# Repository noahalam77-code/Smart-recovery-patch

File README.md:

# TheraPatch

## Repository file structure
- BOM: JCLPCB BOM & regular BOM
- CADfiles: STEP files, STL files, and assembly notes
- PCB: PCB files, Gerber files, schematic images, and PCB images
- Firmware: Code & flashing instructions

## What it is
TheraPatch is a handheld therapeutic device designed to help mitigate the effects of injuries such as bruises, sprains, minor cuts, and more. By using a reverse-polarity system via an H-bridge, TheraPatch can heat the affected area (dilating blood vessels) or cool it (constricting blood vessels), both of which have been shown to help with injury healing at certain temperatures (which TheraPatch can achieve). 

## Motivation
I created TheraPatch with the primary motivation of helping people with common sports/activty related injuries while maintaining an efficient device to do so. Most of the time, when you have a bruise or scrape, you'd rely on disposable ice packs or inefficient heating pads, which are wasteful and time-consuming for long-term use. TheraPatch offers an effective, infinitely reusable solution to this. Instead of freezing water for 3-4 hours or boiling a heatpack everytime you need to reuse it, all you do with TheraPatch is plug and play. It's effective for athletes and normal people.

## Use of TheraPatch
To use the TheraPatch, first ensure your battery/wall adapter is plugged in. Then locate the 4 buttons on the top of the device; these buttons will allow you to set your desired parameters by moving through the menus: mode (hot/cold), set temp, and set time. After your desired settings are set, click the start button to initiate your therapy session, and place the side with the Peltier facing out against the affected area

## How it works
The TheraPatch looks like a simple black-and-white hot-cold block, but its guts are far more advanced. In electronics, generating heat is relatively simple. Electrons bump into each other rapidly in the wire, vibrating and thus creating the heat we feel. This is the easy part; cooling is the real engineering challenge. To cool it, I used a Peltier module, which transfers heat from one side to the other. Now, this needs to be driven by a heatsink and a fan to effectively cool. To achieve heating and cooling on the same side, I used an H bridge. The H-bridge module reverses the polarity in a Peltier module, meaning that when one side is positive and the other is negative, it cools; vice versa. All of this is controlled by a custom 4-layer PCB I designed in KiCad, with an ATmega328P as my microcontroller. The firmware reads a thermistor pressed against the Peltier plate and uses a bang-bang controller to turn the Peltier on/off to reach the desired temperature. This is all run by a rechargeable 12V battery, which charges via USB-C or a 12V wall adapter. These components are combined in a logical order in a CAD-designed box with a hole for all the input plugs and vent fans for air circulation.

Here are images of my project

## CAD imgaes:

## Link to Onshape case:

https://cad.onshape.com/documents/d627d659f05dae60588ec801/w/ad74ef98cd2d7a13cb59f9ec/e/f50ed022a94792dc2cfe6130?renderMode=0&uiState=6a4947abb17d022f5d41873a

# PCB (Signal Layer and ground):

## F.cu (signal traces and ground):

## In1.cu(ground):

## In2.cu (5V & 12V power)

## B.cu (signal traces and ground):

## 3D:

# Schematic (wiring diagram):

## Pic_1:

## Pwr:

## BOM(main)

| Item | Quantity | Unit price | Total price | Descrption | Link |
|------|----------|-----------|-------------|------------|------|
| Fan | 1 | 4.81 | 4.81 | Facliate heaitng & cooling | [Link](https://www.aliexpress.us/item/3256808462428286.html?spm=a2g0o.productlist.main.1.6babkeHNkeHNko&algo_pvid=c39052da-f6dd-4b67-816a-d90e786c586d&algo_exp_id=c39052da-f6dd-4b67-816a-d90e786c586d-0&pdp_ext_f=%7B%22order%22%3A%2262%22%2C%22eval%22%3A%221%22%2C%22fromPage%22%3A%22search%22%7D&pdp_npi=6%40dis%21USD%2111.50%214.79%21%21%2178.10%2132.53%21%402101d6ff17774285328603962e8757%2112000046088904920%21sea%21US%210%21ABX%211%210%21n_tag%3A-29910%3Bd%3Ad6b644bf%3Bm03_new_user%3A-29895%3BpisId%3A5000000204886261&curPageLogUid=VweLjIS1lGkI&utparam-url=scene%3Asearch%7Cquery_from%3A%7Cx_object_id%3A1005008648743038%7C_p_origin_prod%3A) |
| Peltier | 1 | 3.90$ | $3.90 | Cool and heat | [Link](https://www.aliexpress.us/item/3256806863842277.html?src=google&gatewayAdapt=glo2usa) |
| Heatsink | 2 | 4.80$ | $9.79 | Disspate heat | [Link](https://www.amazon.com/Awxlumv-Aluminum-60mmx60mmx15mm-Conductive-Amplifier/dp/B0DNLXD4NL) |
| LCD screen | 1 | 0.9900$ | 0.9900$ | Displaying modes | [Link](https://www.aliexpress.us/item/3256807264700302.html?spm=a2g0o.productlist.main.15.3bb1HGrhHGrhWv&algo_pvid=f071bd73-714c-4717-acaa-3f74ef8deb17&algo_exp_id=f071bd73-714c-4717-acaa-3f74ef8deb17-14&pdp_ext_f=%7B%22order%22%3A%223710%22%2C%22eval%22%3A%221%22%2C%22fromPage%22%3A%22search%22%7D&pdp_npi=6%40dis%21USD%213.14%210.99%21%21%213.14%210.99%21%4021030a6217776832914577048eb84d%2112000040806152744%21sea%21US%210%21ABX%211%210%21n_tag%3A-29910%3Bd%3Ad6b644bf%3Bm03_new_user%3A-29895%3BpisId%3A5000000203537378&curPageLogUid=GNgXD2HWAIP5&utparam-url=scene%3Asearch%7Cquery_from%3A%7Cx_object_id%3A1005007451015054%7C_p_origin_prod%3A#nav-specification) |
| Thermistor | 1 | 0.9500$ | 0.9500$ | Temp meauring | [Link](https://www.adafruit.com/product/4890?srsltid=AfmBOopGi_4mLQSeRw3V9sBgnchAdNrL2zdLeJHItTaAc1rCL6Ne9o2P) |
| Battery | 1 | 26.99$ | $26.99 | Used as main source of power (for moblity) BMS confirmed | [Link](https://liionwholesale.com/products/3s1p-3-7v-3500mah-18650-battery-with-wires-and-connector-lg-mj1-cell-inside?srsltid=AfmBOopbHVjk3o8ywzVI_wQWHKZhMZp1uCq0ynXZWNxGTDKPMvd9ZKI6&variant=31229057794117) |
| Wire | 1 | 2.2300$ | 2.23$ | Battery caddy, peliter and fan extesion | [Link](https://www.aliexpress.us/item/3256802140205012.html?spm=a2g0o.productlist.main.8.4437dfNPdfNPLw&aem_p4p_detail=202606281750527933413825797320002756170&algo_pvid=c53e4217-68c6-4b26-9b29-3624128716f9&algo_exp_id=c53e4217-68c6-4b26-9b29-3624128716f9-7&pdp_ext_f=%7B%22order%22%3A%22123%22%2C%22eval%22%3A%221%22%2C%22fromPage%22%3A%22search%22%7D&pdp_npi=6%40dis%21USD%214.70%212.79%21%21%214.70%212.79%21%402103212b17826942522901169e02c1%2112000052586672765%21sea%21US%210%21ABX%211%210%21n_tag%3A-29910%3Bd%3Ad6b644bf%3Bm03_new_user%3A-29895%3BpisId%3A5000000208023469&curPageLogUid=CY0b8Pvel5HR&utparam-url=scene%3Asearch%7Cquery_from%3A%7Cx_object_id%3A1005002326519764%7C_p_origin_prod%3A&search_p4p_id=202606281750527933413825797320002756170_2) |
| Wall adapter | 1 | $1.28 | $1.28 | 2nd way of recving power (1st battery) | [Link](https://www.aliexpress.us/item/3256806555593510.html?spm=a2g0o.productlist.main.5.103eNCpVNCpVMj&algo_pvid=3d352d1e-bc43-4e77-9d29-16e4344ed46b&algo_exp_id=3d352d1e-bc43-4e77-9d29-16e4344ed46b-4&pdp_ext_f=%7B%22order%22%3A%221992%22%2C%22eval%22%3A%221%22%2C%22fromPage%22%3A%22search%22%7D&pdp_npi=6%40dis%21USD%2111.78%211.28%21%21%2179.73%218.69%21%402101eecd17826947715547891e5012%2112000038157481542%21sea%21US%210%21ABX%211%210%21n_tag%3A-29910%3Bd%3Ad6b644bf%3Bm03_new_user%3A-29895%3BpisId%3A5000000209510139&curPageLogUid=H50idJ0yOZub&utparam-url=scene%3Asearch%7Cquery_from%3A%7Cx_object_id%3A1005006741908262%7C_p_origin_prod%3A) |
| M2 screw 8mm | 100 | 0.0100$ | $1.35 | screws for battery caddy | [Link](https://www.aliexpress.us/item/2251832857570651.html?spm=a2g0o.productlist.main.3.4e3cdUVEdUVEfl&algo_pvid=ea8d64ad-4af7-4109-af97-4e674e97f9e5&algo_exp_id=ea8d64ad-4af7-4109-af97-4e674e97f9e5-2&pdp_ext_f=%7B%22order%22%3A%2216288%22%2C%22eval%22%3A%221%22%2C%22fromPage%22%3A%22search%22%7D&pdp_npi=6%40dis%21USD%211.35%210.99%21%21%211.35%210.99%21%402103129f17825915196483426e5a8e%2112000020018123413%21sea%21US%210%21ABX%211%210%21n_tag%3A-29910%3Bd%3Ad6b644bf%3Bm03_new_user%3A-29895%3BpisId%3A5000000208023469&curPageLogUid=WMcjfyJWRpdQ&utparam-url=scene%3Asearch%7Cquery_from%3A%7Cx_object_id%3A33043885403%7C_p_origin_prod%3A) |
| M2 screw 14mm | 100 | 0.0100$ | $1.35 | screws for main case | [Link](https://www.aliexpress.us/item/2251832857570651.html?spm=a2g0o.productlist.main.3.4e3cdUVEdUVEfl&algo_pvid=ea8d64ad-4af7-4109-af97-4e674e97f9e5&algo_exp_id=ea8d64ad-4af7-4109-af97-4e674e97f9e5-2&pdp_ext_f=%7B%22order%22%3A%2216288%22%2C%22eval%22%3A%221%22%2C%22fromPage%22%3A%22search%22%7D&pdp_npi=6%40dis%21USD%211.35%210.99%21%21%211.35%210.99%21%402103129f17825915196483426e5a8e%2112000020018123413%21sea%21US%210%21ABX%211%210%21n_tag%3A-29910%3Bd%3Ad6b644bf%3Bm03_new_user%3A-29895%3BpisId%3A5000000208023469&curPageLogUid=WMcjfyJWRpdQ&utparam-url=scene%3Asearch%7Cquery_from%3A%7Cx_object_id%3A33043885403%7C_p_origin_prod%3A) |
| Dupont connectors | 40 | 0.0253$ | 1.01$ | connectors for LCD and ISP proggarmer | [Link](https://www.aliexpress.us/item/3256809185840584.html?spm=a2g0o.productlist.main.4.7725T11aT11aC1&aem_p4p_detail=202606272107031134387990076280002008158&algo_pvid=84f900fb-1f7e-4029-80e1-2e2e9eab2415&algo_exp_id=84f900fb-1f7e-4029-80e1-2e2e9eab2415-3&pdp_ext_f=%7B%22order%22%3A%22686%22%2C%22eval%22%3A%221%22%2C%22fromPage%22%3A%22search%22%7D&pdp_npi=6%40dis%21USD%211.56%211.01%21%21%2110.57%216.87%21%402101e80317826196231237198ed5a5%2112000048899602396%21sea%21US%210%21ABX%211%210%21n_tag%3A-29910%3Bd%3Ad6b644bf%3Bm03_new_user%3A-29895%3BpisId%3A5000000208023469&curPageLogUid=48BAjk6LrSZa&utparam-url=scene%3Asearch%7Cquery_from%3A%7Cx_object_id%3A1005009372155336%7C_p_origin_prod%3A&search_p4p_id=202606272107031134387990076280002008158_2) |
| ISP porgrammer | 1 | 1.9100$ | $1.91 | Flashes code onto the ATMega chip | [Link](https://www.aliexpress.us/item/3256810618247711.html?spm=a2g0o.productlist.main.2.71a9WonxWonxOW&algo_pvid=013dc172-5dcd-4517-a7dc-e44b31c61f77&algo_exp_id=013dc172-5dcd-4517-a7dc-e44b31c61f77-1&pdp_ext_f=%7B%22order%22%3A%2220%22%2C%22eval%22%3A%221%22%2C%22fromPage%22%3A%22search%22%7D&pdp_npi=6%40dis%21USD%212.41%211.91%21%21%212.41%211.91%21%402101d6ff17826055513113304ea732%2112000053555380165%21sea%21US%210%21ABX%211%210%21n_tag%3A-29910%3Bd%3Ad6b644bf%3Bm03_new_user%3A-29895%3BpisId%3A5000000208023469&curPageLogUid=atD9pSQGrkCO&utparam-url=scene%3Asearch%7Cquery_from%3A%7Cx_object_id%3A1005010804562463%7C_p_origin_prod%3A) |
| Buttons | 20 | 0.1095$ | 2.19$ | Switching between menus & 0start/stop | [Link](https://www.aliexpress.us/item/3256801638385730.html?spm=a2g0o.productlist.main.18.6eae9KoY9KoY39&algo_pvid=a04722e0-ab76-4104-b323-04a47393d95b&algo_exp_id=a04722e0-ab76-4104-b323-04a47393d95b-17&pdp_ext_f=%7B%22order%22%3A%2239%22%2C%22eval%22%3A%221%22%2C%22fromPage%22%3A%22search%22%7D&pdp_npi=6%40dis%21USD%213.15%212.59%21%21%213.15%212.59%21%402101eee917825893617621165ec559%2112000017947649837%21sea%21US%210%21ABX%211%210%21n_tag%3A-29910%3Bd%3Ad6b644bf%3Bm03_new_user%3A-29895%3BpisId%3A5000000208023469&curPageLogUid=ypVEuRkxBtEG&utparam-url=scene%3Asearch%7Cquery_from%3A%7Cx_object_id%3A1005001824700482%7C_p_origin_prod%3A) |
| Terminal Block | 5 | 0.0864$ | 0.4300$ | For conencting things without JST conenctor | [Link](https://www.lcsc.com/product-detail/C394556.html?s_z=n_JILN%2520JL126-50002G01) |
| Barrel Jack | 5 | 0.1462$ | $0.73 | Wall power input | [Link](https://www.lcsc.com/product-detail/C720558.html?s_z=n_q_barrel%2520jack%25205A&spm=wm.fly.bg.0.xh&lcsc_vid=QFJaAQFeTlFdU1xXTwILAlBQQQILVwYAQQALAlYEFFYxVlNRTlVfU1NRRlVfXzsOAxUeFF5JWBYZEEoKFBINSQcJGk4NBhADEA4cHktRRVBADxALGw%3D%3D) |
| JST female | 20 | 0.0403$ | 0.81$ | Battery inpt | [Link](https://www.lcsc.com/product-detail/C158012.html?s_z=n_q_C158012&globalKeyword=C158012) |
| 4 Pin connector for LCD | 10 | 0.0807$ | 0.81$ | LCD input | [Link](https://www.lcsc.com/product-detail/C50950.html?s_z=n_q_C50950&globalKeyword=C50950) |
| Arundio flash input | 5 | 0.2238$ | 1.12$ | Pins to flash code | [Link](https://www.lcsc.com/product-detail/C50980.html?s_z=n_q_C50980&globalKeyword=C50980) |
| USB-C | 5 | $0.1857 | $0.93 | Charging | [Link](https://www.lcsc.com/product-detail/C165948.html?s_z=n_q_C165948&globalKeyword=C165948) |
| 5A fuse | 10 | 0.0506$ | $0.51 | PCB | [Link](https://www.lcsc.com/product-detail/C41367229.html?s_z=n_q_t_5A%2520smd%2520fuse&spm=wm.fly.bg.0.xh___wm.ssy.tc.1.tz&lcsc_vid=QFJaAQFeTlFdU1xXTwILAlBQQQILVwYAQQALAlYEFFYxVlNRX1JWRFhbVTsOAxUeFF5JWBYZEEoKFBINSQcJGk4eFQsCAgIaSgADAwAHC0slQ1hcUV1ST1ZADxALGw%3D%3D) |
| 16 Mhz cyrstal | 5 | 0.2372$ | $1.19 | PCB | [Link](https://www.lcsc.com/product-detail/C122519.html?s_z=n_q_C122519&globalKeyword=C122519) |
| Ferrite Bead | 10 | 0.0262$ | $0.26 | PCB | [Link](https://www.lcsc.com/product-detail/C21519.html?s_z=n_q_600%2520ohm%2520ferrite%2520bead%25200805&spm=wm.fly.bg.0.xh&lcsc_vid=QFJaAQFeTlFdU1xXTwILAlBQQQILVwYAQQALAlYEFFYxVlNRTlNeUFZWRFZaXjsOAxUeFF5JWBYZEEoKFBINSQcJGk4eFQsCAgIaSgADAwAHC0slQFFbUVZIHxUDCw%3D%3D) |
| AO3400A | 5 | 0.0846$ | $0.42 | diode for the fan | [Link](https://www.lcsc.com/product-detail/C20917.html?s_z=n_q_C20917&globalKeyword=C20917) |
| SS54 Diode | 10 | 0.0366$ | 0.3700$ | Diode used in buck and input pwr | [Link](https://www.lcsc.com/product-detail/C22452.html?s_z=n_q_SS54%2520diode&spm=wm.fly.bg.0.xh&lcsc_vid=QFJaAQFeTlFdU1xXTwILAlBQQQILVwYAQQALAlYEFFYxVlNRTlNaVVRURldfUzsOAxUeFF5JWBYZEEoKFBINSQcJGk4eFQsCAgIaSgADAwAHC0slT1dZUUoOAwwC) |
| 33uH buck Inductor | 5 | 0.2204$ | 1.10$ | PCB | [Link](https://www.lcsc.com/product-detail/C9400.html?s_z=n_q_t_33uH%2520SMD%2520ind&spm=wm.fly.bg.0.xh___wm.ssy.tc.0.tz&lcsc_vid=QFJaAQFeTlFdU1xXTwILAlBQQQILVwYAQQALAlYEFFYxVlNRT1leX1JUQFNXUTsOAxUeFF5JWBYZEEoKFBINSQcJGk4dAgUUFAk%3D) |
| 2.2uH boost Inductor | 5 | 0.1161$ | $0.58 | PCB | [Link](https://www.lcsc.com/product-detail/C7461347.html?s_z=n_q_CXP0530-2R2M-AG&spm=wm.fly.bg.0.xh&lcsc_vid=QFJaAQFeTlFdU1xXTwILAlBQQQILVwYAQQALAlYEFFYxVlNRT1leX11TRlhaUjsOAxUeFF5JWBYZEEoKFBINSQcJGk4NBhADEA4cHktXRllfSQwSGg0%3D) |
| 120K resistor | 100 | $0.0022 | $0.22 | PCB | [Link](https://www.lcsc.com/product-detail/C2907223.html?s_z=n_q_C2907223&globalKeyword=C2907223) |
| 90K resitor | 10 | $0.0654 | $0.65 | PCB | [Link](https://www.lcsc.com/product-detail/C5123603.html?s_z=n_q_C5123603&globalKeyword=C5123603) |
| 68K resistor | 100 | $0.0021 | $0.21 | PCB | [Link](https://www.lcsc.com/product-detail/C2907283.html?s_z=n_q_C2907283&globalKeyword=C2907283) |
| 51k resistor | 100 | $0.0021 | $0.21 | PCB | [Link](https://www.lcsc.com/product-detail/C2933461.html?s_z=n_q_C2933461&globalKeyword=C2933461) |
| 47K resistor | 100 | $0.0021 | $0.21 | PCB | [Link](https://www.lcsc.com/product-detail/C2930202.html?s_z=n_q_C2930202&globalKeyword=C2930202) |
| 10K resistor | 100 | $0.0020 | $0.20 | PCB | [Link](https://www.lcsc.com/product-detail/C2907219.html?s_z=n_q_C2907219&globalKeyword=C2907219) |
| 5.1K resistor | 100 | $0.00 | $0.27 | PCB | [Link](https://www.lcsc.com/product-detail/C27834.html?s_z=n_q_C27834&globalKeyword=C27834) |
| 3.3K resistor | 100 | $0.0020 | $0.20 | PCB | [Link](https://www.lcsc.com/product-detail/C2907023.html?s_z=n_q_t_3.3K%2520resistor&spm=wm.fly.bg.1.xh___wm.ssy.tc.0.tz&lcsc_vid=QFJaAQFeTlFdU1xXTwILAlBQQQILVwYAQQALAlYEFFYxVlNRT1lfUVBUTlNfXzsOAxUeFF5JWBYZEEoKFBINSQcJGk4eFQsCAgIaSgADAwAHC0slRVZWVFBIHxUDCw%3D%3D) |
| 1k resistor | 100 | $0.0076 | $0.76 | PCB | [Link](https://www.lcsc.com/product-detail/C2907002.html?s_z=n_q_t_0603%25201k%25CE%25A9%2520&spm=wm.fly.bg.0.xh___wm.ssy.tc.0.tz&lcsc_vid=QFJaAQFeTlFdU1xXTwILAlBQQQILVwYAQQALAlYEFFYxVlNeRFBXUFRQT1NcUzsOAxUeFF5JWBYZEEoKFBINSQcJGk4NBhADEA4cHktXRlhXSQwSGg0%3D) |
| 100Ω resistor | 100 | $0.0014 | $0.14 | PCB | [Link](https://www.lcsc.com/product-detail/C105588.html?s_z=n_q_t_100%25CE%25A9%2520resistor&spm=wm.fly.bg.0.xh___wm.ssy.tc.0.tz&lcsc_vid=QFJaAQFeTlFdU1xXTwILAlBQQQILVwYAQQALAlYEFFYxVlNRT1lfUVxWQ1RbXzsOAxUeFF5JWBYZEEoKFBINSQcJGk4NBhADEA4cHktXRlhXSQwSGg0%3D) |
| 470uF capacitor | 5 | $0.0875 | $0.44 | PCB | [Link](https://www.lcsc.com/product-detail/C976030.html) |
| 220uF capacitor | 10 | $0.0276 | $0.28 | PCB | [Link](https://www.lcsc.com/product-detail/C22388075.html?s_z=n_q_220uF%2520%25C2%25B120%2525%252025V%2520Aluminum%2520Electrolytic%2520Capacitors%2520SMD&spm=wm.fly.bg.0.xh&lcsc_vid=QFJaAQFeTlFdU1xXTwILAlBQQQILVwYAQQALAlYEFFYxVlNRT1lfUFxUQ1NdVjsOAxUeFF5JWBYZEEoKFBINSQcJGk4NBhADEA4cHktXRlVeSQwSGg0%3D) |
| 100uF capacitor | 20 | $0.0372 | $0.74 | PCB | [Link](https://www.lcsc.com/product-detail/C970685.html?s_z=n_q_C970685&globalKeyword=C970685) |
| 22uF capacitor | 20 | $0.0349 | $0.70 | PCB | [Link](https://www.lcsc.com/product-detail/C45783.html?s_z=n_q_C45783&globalKeyword=C45783) |
| 10uF capacitor | 10 | $0.0394 | $0.39 | PCB | [Link](https://www.lcsc.com/product-detail/C9807.html?s_z=n_q_10uF%2520%25C2%25B110%2525%252025V%2520Ceramic%2520Capacitor&spm=wm.fly.bg.0.xh&lcsc_vid=QFJaAQFeTlFdU1xXTwILAlBQQQILVwYAQQALAlYEFFYxVlNRT1lfUFNSQVNXVDsOAxUeFF5JWBYZEEoKFBINSQcJGk4eFQsCAgIaSgADAwAHC0slRlRWUlRIHxUDCw%3D%3D) |
| 1uF capacitor | 50 | $0.0069 | $0.35 | PCB | [Link](https://www.lcsc.com/product-detail/C29936.html?s_z=n_q_1uF%2520%25C2%25B110%2525%252025V%2520Ceramic%2520Capacitor%2520&spm=wm.fly.bg.0.xh&lcsc_vid=QFJaAQFeTlFdU1xXTwILAlBQQQILVwYAQQALAlYEFFYxVlNRT1lfUFBfTlhZUTsOAxUeFF5JWBYZEEoKFBINSQcJGk4eFQsCAgIaSgADAwAHC0slQlBXXlxRRU8GEwkK) |
| 0.1uF capacitor | 100 | $0.004 | $0.40 | PCB | [Link](https://www.lcsc.com/product-detail/C1590.html?s_z=n_q_100nF%2520%25C2%25B110%2525%252025V%2520Ceramic%2520Capacitor%2520&spm=wm.fly.bg.0.xh&lcsc_vid=QFJaAQFeTlFdU1xXTwILAlBQQQILVwYAQQALAlYEFFYxVlNRT1lfUFFfRVVdVzsOAxUeFF5JWBYZEEoKFBINSQcJGk4eFQsCAgIaSgADAwAHC0slRlVYUVdIHxUDCw%3D%3D) |
| 22pF capacitor | 100 | $0.0041 | $0.41 | PCB | [Link](https://www.lcsc.com/product-detail/C1653.html?s_z=n_q_C1653&globalKeyword=C1653) |
| ST VNH5019ATR-E | 1 | 9.36$ | 9.36$ | H-bridge to switch polairty | [Link](https://www.lcsc.com/product-detail/C2653552.html?s_z=n_VNH5019A-E&spm=wm.ssy.bg.0.stp&lcsc_vid=QFJaAQFeTlFdU1xXTwILAlBQQQILVwYAQQALAlYEFFYxVlNRQ1VZV1NQRFZcUjsOAxUeFF5JWBYZEEoKFBINSQcJGk4eFQsCAgIaSgADAwAHC0slQlJZUlRIHxUDCw%3D%3D) |
| LM2596S-5.0 | 1 | 1.42$ | 1.37$ | Buck convetor for non 12V parts | [Link](https://www.lcsc.com/product-detail/C116713.html?s_z=n_LM2596S-5&spm=wm.ssy.bg.17.xh&lcsc_vid=QFJaAQFeTlFdU1xXTwILAlBQQQILVwYAQQALAlYEFFYxVlNRQ1VZVVdQR1leVjsOAxUeFF5JWBYZEEoKFBINSQcJGk4eFQsCAgIaSgADAwAHC0slRlRdVVZUWQkaCgg%3D) |
| WCH CH224K | 1 | $0.61 | $0.61 | Power negogatior, Requests 9V | [Link](https://www.lcsc.com/product-detail/C970725.html?s_z=n_q_CH224K&spm=wm.ssy.bg.0.xh&lcsc_vid=QFJaAQFeTlFdU1xXTwILAlBQQQILVwYAQQALAlYEFFYxVlNRQFZaUldfQlhfVjsOAxUeFF5JWBYZEEoKFBINSQcJGk4dAgUUFAk%3D) |
| IP2326 | 1 | $0.62 | $0.62 | Boost converter for charging 9V to 12.6V | [Link](https://www.lcsc.com/product-detail/C2832094.html?s_z=n_q_IP2326&spm=wm.fly.bg.0.xh&lcsc_vid=QFJaAQFeTlFdU1xXTwILAlBQQQILVwYAQQALAlYEFFYxVlNRT1lfVVxfQFdeXzsOAxUeFF5JWBYZEEoKFBINSQcJGk4eFQsCAgIaSgADAwAHC0slTlZeUFZTWQkaCgg%3D) |
| ATMEGA328P-AU | 1 | $2.65 | $2.65 | Microcontroller | [Link](https://www.lcsc.com/product-detail/C14877.html?s_z=n_q_ATmega328P-A&spm=wm.fly.bg.0.xh&lcsc_vid=QFJaAQFeTlFdU1xXTwILAlBQQQILVwYAQQALAlYEFFYxVlNRT1lfVFReT1FZVTsOAxUeFF5JWBYZEEoKFBINSQcJGk4eFQsCAgIaSgADAwAHC0slRVldVVRfQ08GEwkK) |

## BOM(JLCPCB)

| Comment | Designator | Footprint | LCSC Part Number |
|---------|-----------|-----------|------------------|
| USB-C | USBC1 | USBC_U:USB-C_SMD-TYPE-C-31-M-12_1 | C165948 |
| 5A Fuse | F2 | Fuse:Fuse_1206_3216Metric | C41367229 |
| Crystal | Y1 | Crystal:Crystal_SMD_5032-2Pin_5.0x3.2mm | C122519 |
| Ferrite bead | FB1 | Inductor_SMD:L_0805_2012Metric | C21519 |
| AO3400A diode | Q4 | Package_TO_SOT_SMD:SOT-23 | C20917 |
| SS54 Diode | D1, D2, D3, D6 | Diode_SMD:D_SMA | C22452 |
| 33µH inductor | L1 | inductor_33uh:IND-SMD_L12.3-W12.3 | C9400 |
| 120K Resitor | R21, R35 | Resistor_SMD:R_0805_2012Metric | C2907223 |
| 90K Resitor | R24 | Resistor_SMD:R_0805_2012Metric | C5123603 |
| 68K Resitor | R22 | Resistor_SMD:R_0805_2012Metric | C2907283 |
| 51K Resitor | R20 | Resistor_SMD:R_0805_2012Metric | C2933461 |
| 47K restior | R27 | Resistor_SMD:R_0805_2012Metric | C2930202 |
| 10K Restior | R34, R33, R28, R16, R13, R12, R10, R9, R8, R5, R3, R2, R1 | Resistor_SMD:R_0805_2012Metric | C2907219 |
| 5.1K resistor | R18, R19 | Resistor_SMD:R_0805_2012Metric | C27834 |
| 3.3K resistor | R7, R14 | Resistor_SMD:R_0603_1608Metric | C2907023 |
| 1k resistor | R32, R23, R17, R15, R6, R4 | Resistor_SMD:R_0603_1608Metric | C2907002 |
| 100Ω resistor | R11 | Resistor_SMD:R_0603_1608Metric | C105588 |
| 220uF capacitor | C2 | Capacitor_SMD:CP_Elec_6.3x7.7 | C22388075 |
| 100uF capacitor | C8 | Capacitor_SMD:CP_Elec_6.3x7.7 | C970685 |
| 22uF capacitor | C14, C17 | Capacitor_SMD:C_0805_2012Metric | C45783 |
| 10uF capacitor | C25, C23, C22,C10 | Capacitor_SMD:C_1206_3216Metric | C9807 |
| 1uF capacitor | C7 | Capacitor_SMD:C_0603_1608Metric | C29936 |
| 0.1uF capacitor | C24, C19, C18, C15, C13, C12, C11, C9, C6, C5, C4, C3, C1 | Capacitor_SMD:C_0603_1608Metric | C1590 |
| 22pF capacitor | C20,C21 | Capacitor_SMD:C_0603_1608Metric | C1653 |
| ST VNH5019ATR-E | U2 | Package_SO:ST_MultiPowerSO-30 | C2653552 |
| LM2596S-5.0 | U1 | Package_TO_SOT_SMD:TO-263-5_TabPin3 | C116713 |
| WCH CH224K | U3 | CH224K:ESSOP-10_L4.9-W3.9-P1.0-LS6.0-TL-EP | C970725 |
| IP2326 | U5 | Package_DFN_QFN:QFN-24-1EP_4x4mm_P0.5mm_EP2.6x2.6mm | C2832094 |
| ATMEGA328P-AU | U4 | Package_QFP:TQFP-32_7x7mm_P0.8mm | C14877 |

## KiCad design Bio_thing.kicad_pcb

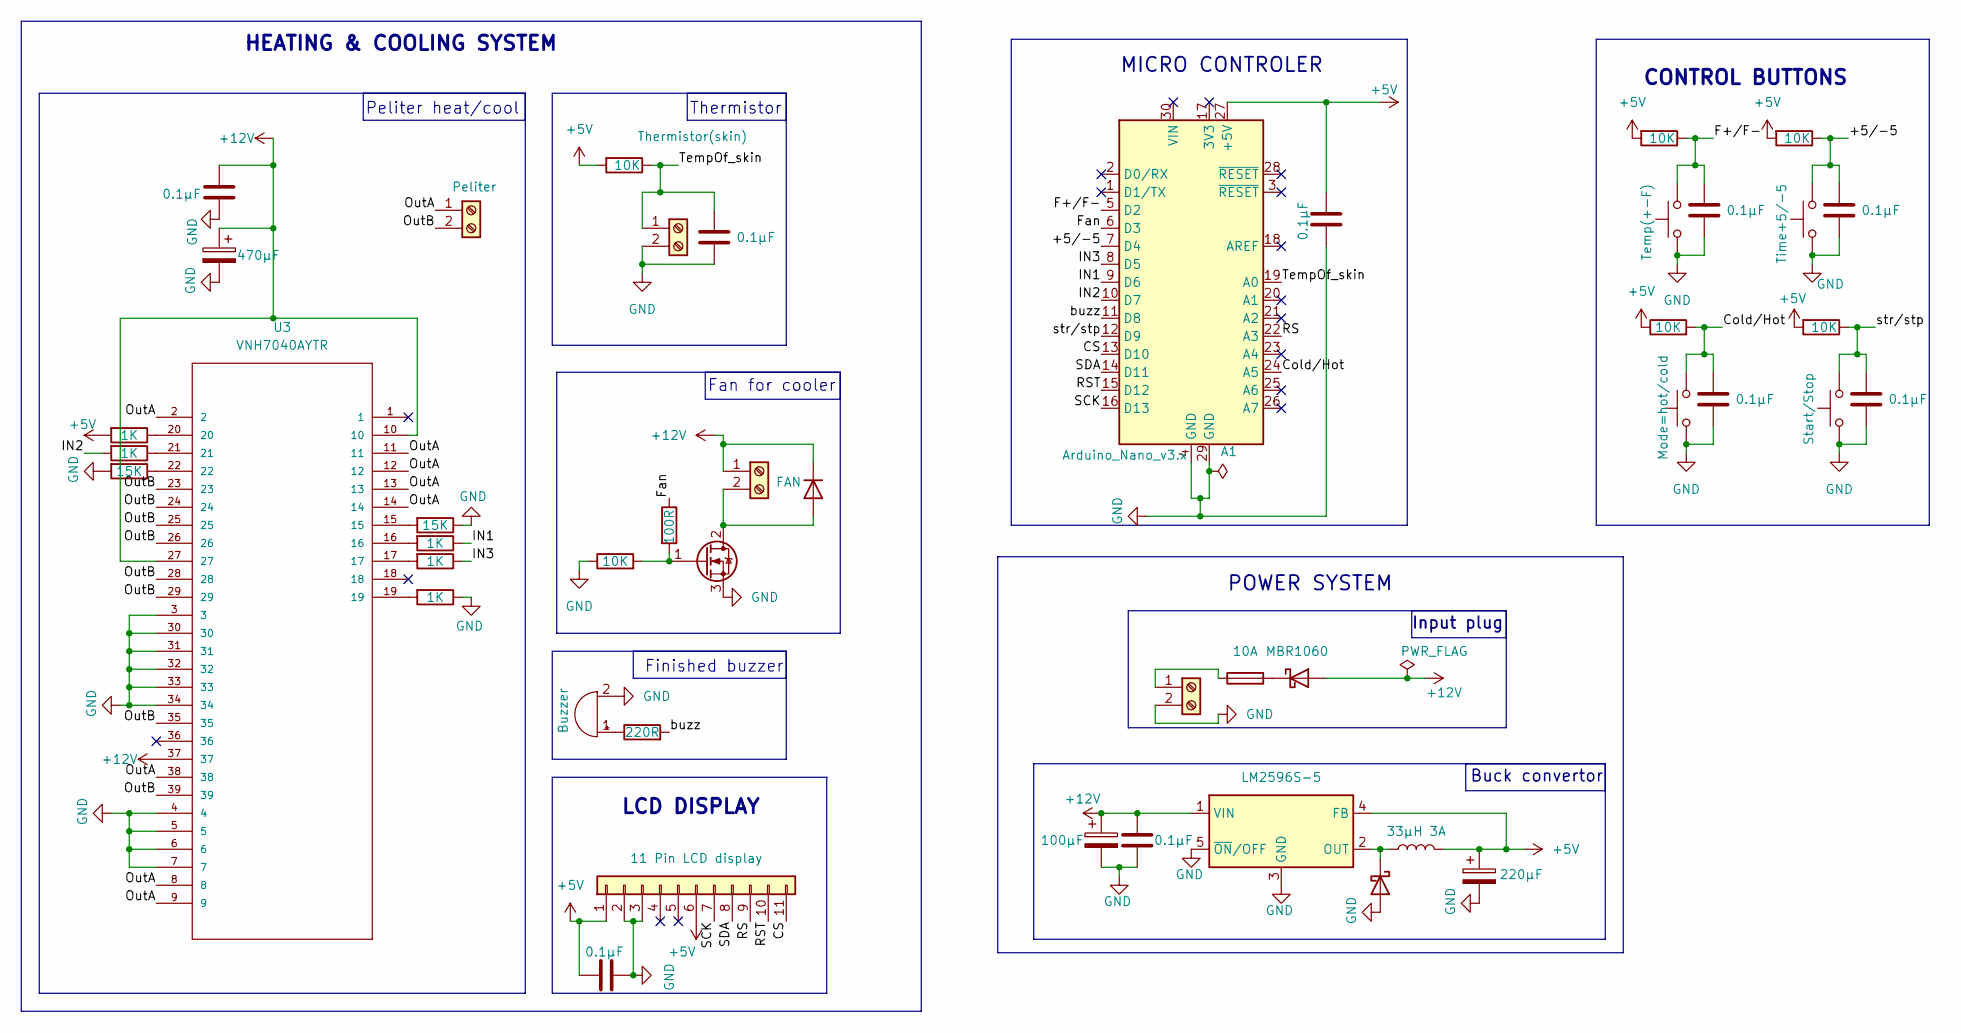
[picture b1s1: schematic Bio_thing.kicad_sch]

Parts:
A1: Arduino_Nano_v3.x; Untitled
BZ1: Buzzer; Buzzer_12x9.5RM7.6
C1, C3, C4, C5, C6, C9, C10, C11, C15: 0.1µF; C_0805_2012Metric
C2: 220µF; CP_Elec_6.3x7.7
C8: 100µF; C_1206_3216Metric
C16: 470µF; CP_Elec_8x10.5
D1: 1N4001; D_SMA_Handsoldering
D2: 1N5822; D_SMA_Handsoldering
D4: MBR1060; TO-220-2_Vertical
F2: 10A; Fuseholder_Cylinder-5x20mm_Schurter_0031_8201_Horizontal_Op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
Fan_for_cooler1: IRLB8721PBF; TO-220-3_Vertical
J1: FAN; TerminalBlock_Phoenix_PT-1,5-2-5.0-H_1x02_P5.00mm_Horizontal
J2: Peliter; TerminalBlock_Phoenix_PT-1,5-2-5.0-H_1x02_P5.00mm_Horizontal
J3: Screw_Terminal_01x02; TerminalBlock_Phoenix_PT-1,5-2-5.0-H_1x02_P5.00mm_Horizontal
J5: Thermistor(skin); TerminalBlock_Phoenix_PT-1,5-2-5.0-H_1x02_P5.00mm_Horizontal
J8: 11 Pin LCD display; PinSocket_1x11_P2.54mm_Vertical
L1: 33µH 3A; L_Radial_D8.7mm_P5.00mm_Fastron_07HCP
R1, R2, R3, R8, R9, R10: 10K; R_0805_2012Metric
R4, R5, R6, R7, R19: 1K; R_0805_2012Metric
R11: 100R; R_0805_2012Metric
R12, R14: 15K; R_0805_2012Metric
R13: 220R; R_0805_2012Metric
SW2: Mode=hot/cold; SW_PUSH_6mm_H4.3mm
SW3: Start/Stop; SW_PUSH_6mm_H4.3mm
SW4: Temp(+-F); SW_PUSH_6mm_H4.3mm
SW5: Time+5/-5; SW_PUSH_6mm_H4.3mm
U1: LM2596S-5; TO-263-5_TabPin3
U3: VNH7040AYTR; POWERSSO-36TP_STM; MANUFACTURER_PART_NUMBER VNH7040AYTR

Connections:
+5V: A1.27 (+5V), C2.1, C10.1, C11.2, J8.1, J8.6, L1.2, R2.2, R3.2, R8.2, R9.2, R10.1, R19.2, U1.4 (FB)
+12V: C8.1, C9.1, C15.1, C16.1, D1.1 (K), D4.2 (A), J1.1, U1.1 (VIN), U3.10, U3.27, U3.37
/+5/-5: A1.7 (D4), C6.1, R9.1, SW5.2
/CS: A1.13 (D10), J8.11
/Cold/Hot: A1.24 (A5), C5.1, R10.2, SW2.2
/F+/F-: A1.5 (D2), C3.1, R8.1, SW4.2
/Fan: A1.6 (D3), R11.1
/IN1: A1.9 (D6), R4.1
/IN2: A1.10 (D7), R5.2
/IN3: A1.8 (D5), R6.1
/OutA: J2.1, U3.2, U3.8, U3.9, U3.11, U3.12, U3.13, U3.14, U3.38
/OutB: J2.2, U3.23, U3.24, U3.25, U3.26, U3.28, U3.29, U3.35, U3.39
/RS: A1.22 (A3), J8.9
/RST: A1.15 (D12), J8.10
/SCK: A1.16 (D13), J8.7
/SDA: A1.14 (D11), J8.8
/TempOf_skin: A1.19 (A0), C4.1, J5.1, R2.1
/buzz: A1.11 (D8), R13.2
/str/stp: A1.12 (D9), C1.1, R3.1, SW3.2
GND: A1.4 (GND), A1.29 (GND), BZ1.2 (-), C1.2, C2.2, C3.2, C4.2, C5.2, C6.2, C8.2, C9.2, C10.2, C11.1, C15.2, C16.2, D2.2 (A), Fan_for_cooler1.3 (S), J3.2, J5.2, J8.2, J8.3, R1.1, R7.1, R12.1, R14.2, SW2.1, SW3.1, SW4.1, SW5.1, U1.3 (GND), U1.5 (~ON/OFF), U3.3, U3.4, U3.5, U3.6, U3.7, U3.30, U3.31, U3.32, U3.33, U3.34
unnamed: BZ1.1 (+), R13.1
unnamed: D1.2 (A), Fan_for_cooler1.2 (D), J1.2
unnamed: D2.1 (K), L1.1, U1.2 (OUT)
unnamed: D4.1 (K), F2.2
unnamed: Fan_for_cooler1.1 (G), R1.2, R11.2
unnamed: F2.1, J3.1
unnamed: R4.2, U3.16
unnamed: R5.1, U3.21
unnamed: R6.2, U3.17
unnamed: R7.2, U3.19
unnamed: R12.2, U3.15
unnamed: R14.1, U3.22
unnamed: R19.1, U3.20

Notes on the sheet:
Thermistor
MICRO CONTROLER
Peliter heat/cool
POWER SYSTEM
HEATING & COOLING SYSTEM
LCD DISPLAY
Buck convertor
Finished buzzer
Input plug
Fan for cooler
CONTROL BUTTONS

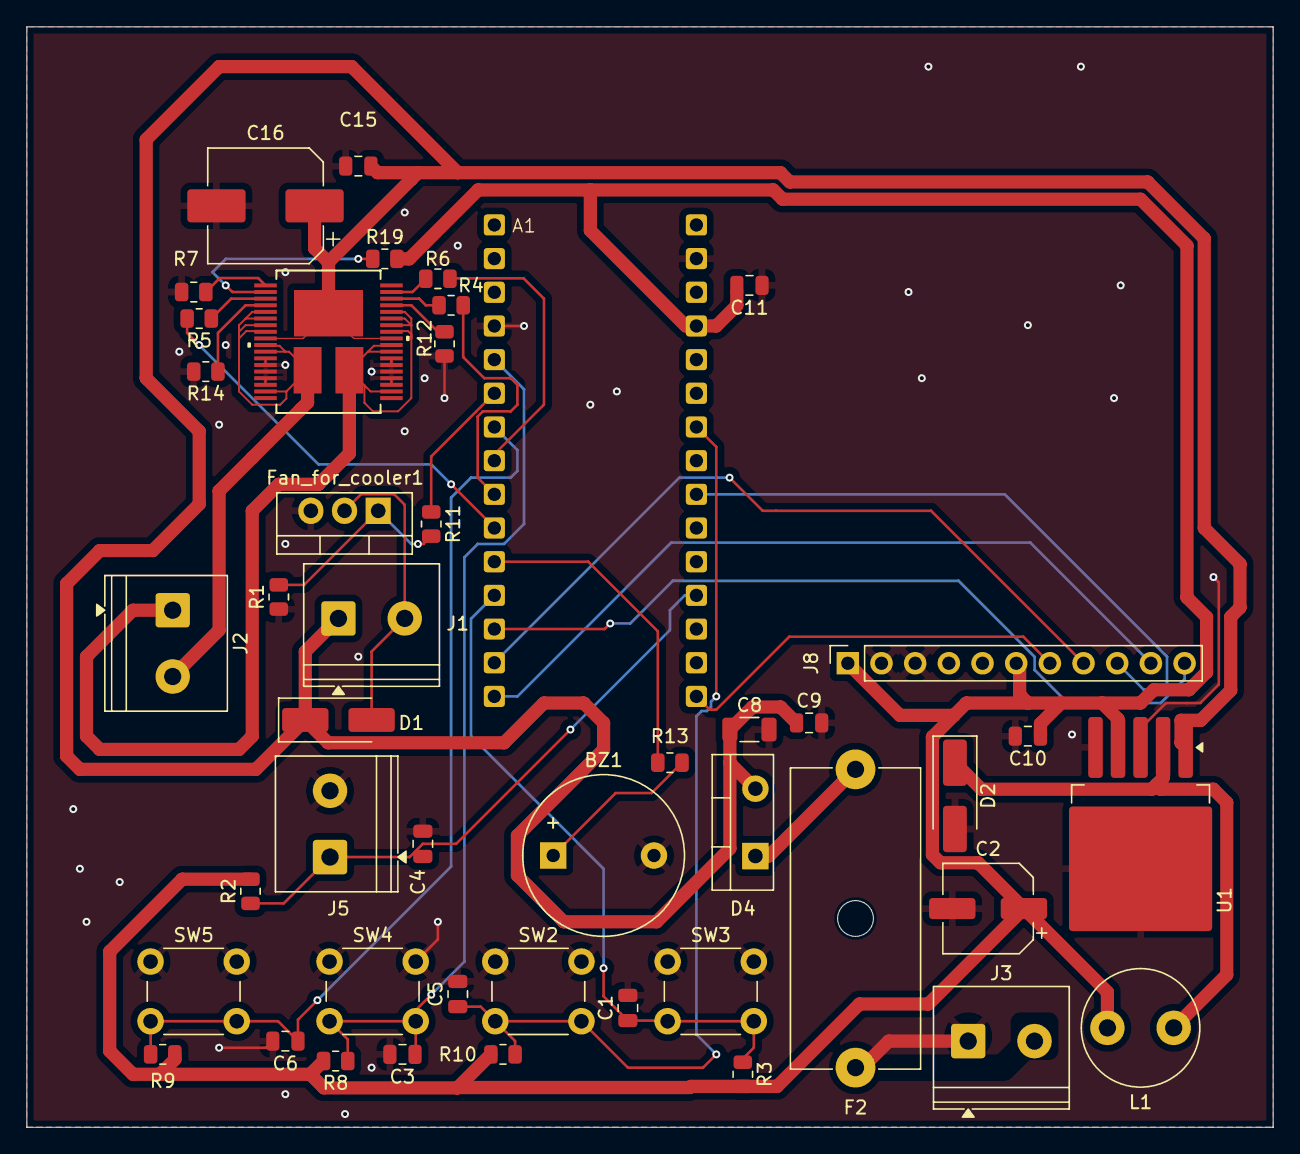
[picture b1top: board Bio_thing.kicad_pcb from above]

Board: 2 copper layers, 94.0 x 83.0 mm, 46 parts (0 on the bottom side), 33 nets.

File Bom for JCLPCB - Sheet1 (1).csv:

Comment,Designator,Footprint,LCSC Part Number
VNH7040AYTR,U3,VNH7040AYTR:POWERSSO-36TP_STM,C2969764
LM2596S-5.0/NOPB,U1,Package_TO_SOT_SMD:TO-263-5_TabPin3,C116713
1N4001,D1,Diode_SMD:D_SMA_Handsoldering,C2909965
1N5822,D2,Diode_SMD:D_SMA_Handsoldering,C8678
15K,"R12, R14",Resistor_SMD:R_0805_2012Metric,C17475
10K,"R1, R2, R3, R8, R9, R10",Resistor_SMD:R_0805_2012Metric,C84376
1K,"R4, R5, R6, R7, R19",Resistor_SMD:R_0805_2012Metric,C95781
220R,R13,Resistor_SMD:R_0805_2012Metric,C17557
100R,R11,Resistor_SMD:R_0805_2012Metric,C17408
0.1µF,"C1, C3, C4, C5, C6, C9, C10, C11, C15",Capacitor_SMD:C_0805_2012Metric,C49678
100 µF,C8,Capacitor_SMD:C_1206_3216Metric,C15008
220 µF,C2,Capacitor_SMD:CP_Elec_6.3x7.7,C4747974
470 µF,C16,Capacitor_SMD:CP_Elec_8x10.5,C48935394

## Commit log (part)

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2026-03-31 Rename Bio_thing.kicad_pcb to pcb/Bio_thing.kicad_pcb
2026-03-31 Rename Bio_thing.kicad_pro to pcb/Bio_thing.kicad_pro
2026-03-31 Rename Bio_thing.kicad_sch to pcb/Bio_thing.kicad_sch
2026-03-31 Rename Pcb3dBttm.png to images/Pcb3dBttm.png
2026-03-31 Rename Pcb3dTop.png to images/Pcb3dTop.png
2026-03-31 Rename Sch.png to images/Sch.png
2026-03-31 Rename pcb.png to images/pcb.png
2026-03-31 Rename gerbers.zip to pcb/gerbers.zip
2026-04-01 Rename Bom for JCLPCB - Sheet1 (1).csv to Bom/Bom for JCLPCB - Sheet1 (1).csv
2026-04-02 Rename CASE.png to CAD/Images/CASE.png
2026-04-02 Rename CaseTop.png to CAD/ImagesCaseTop.png
2026-04-02 Rename CAD/ImagesCaseTop.png to CAD/Images/CaseTop.png
2026-04-02 Rename CAD/Images/CASE.png to CAD /CASE.png
2026-04-02 Rename CAD/Images/CaseTop.png to CAD/CaseTop.png
2026-04-02 Rename CASE.png to CASE.png
2026-04-02 Create LICENSE
2026-04-02 Rename Pcb3dBttm.png to Pcb3dBttm.png
2026-04-02 Rename Pcb3dTop.png to Pcb3dTop.png
2026-04-02 Rename Sch.png to Sch.png
2026-04-02 Rename pcb.png to pcb.png

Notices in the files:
parts and their libraries:
COPYRIGHT: Copyright (C) 2023 Ultra Librarian. All rights reserved.
